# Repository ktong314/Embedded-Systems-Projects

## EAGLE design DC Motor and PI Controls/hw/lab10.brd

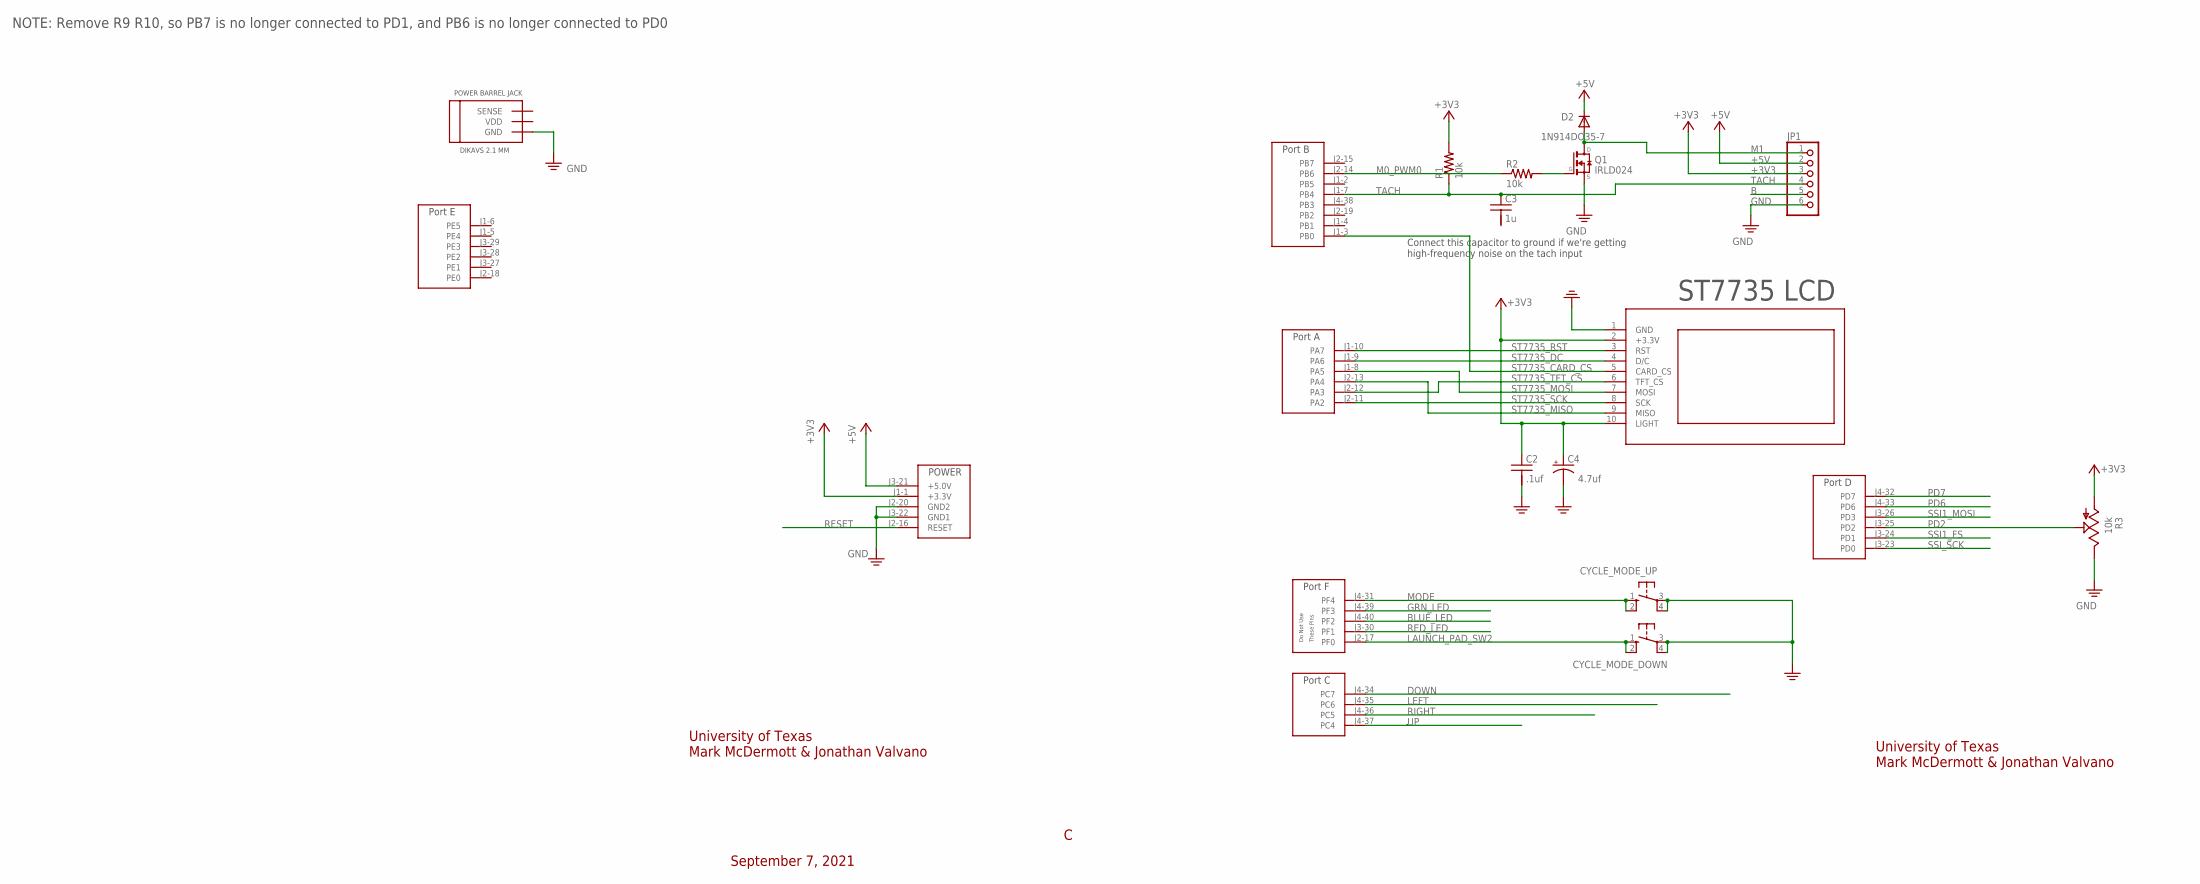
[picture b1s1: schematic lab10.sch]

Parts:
C2: .1uf; CAP200MIL
C3: 1u; CAP100MIL
C4: 4.7uf; CAP200MILPOLARIZED
CYCLE_MODE_DOWN: B3F-1052; B3F-10XX
CYCLE_MODE_UP: B3F-1052; B3F-10XX
D2: 1N914DO35-7; DO35-7
JP1: PINHD-1X6; 1X06
Q1: IRLD024
R1, R2: 10k; RES300MIL
R3: 10k; PTA2043
U$2: TM4C_BP; TM4C_BOOSTER_PACK
U$3: ST7735
U$4: 2.1MM_BARREL_JACK; 2.1M_BARREL_JACK

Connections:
+3V3: C2.1, C4.+, JP1.3, R1.2, R3.3 (A), U$2.J1-1 (+3.3V), U$3.2 (+3.3V), U$3.10 (LIGHT)
+5V: D2.C, JP1.2, U$2.J3-21 (+5.0V)
B: JP1.5
BLUE_LED: U$2.J4-40 (PF2)
DOWN: U$2.J4-34 (PC7)
GND: C2.2, C4.-, CYCLE_MODE_DOWN.3, CYCLE_MODE_DOWN.4 (P1), CYCLE_MODE_UP.3, CYCLE_MODE_UP.4 (P1), JP1.6, Q1.P$4 (S), R3.1 (E), U$2.J2-20 (GND2), U$2.J3-22 (GND1), U$3.1 (GND), U$4.GND
GRN_LED: U$2.J4-39 (PF3)
LAUNCH_PAD_SW2: CYCLE_MODE_DOWN.1 (S), CYCLE_MODE_DOWN.2 (S1), U$2.J2-17 (PF0)
LEFT: U$2.J4-35 (PC6)
M0_PWM0: R2.1, U$2.J2-14 (PB6)
M1: D2.A, JP1.1, Q1.P$1 (D)
MODE: CYCLE_MODE_UP.1 (S), CYCLE_MODE_UP.2 (S1), U$2.J4-31 (PF4)
unnamed: Q1.P$3 (G), R2.2
PD2: R3.2 (S), U$2.J3-25 (PD2)
PD6: U$2.J4-33 (PD6)
PD7: U$2.J4-32 (PD7)
RED_LED: U$2.J3-30 (PF1)
RESET: U$2.J2-16 (RESET)
RIGHT: U$2.J4-36 (PC5)
SSI1_FS: U$2.J3-24 (PD1)
SSI1_MOSI: U$2.J3-26 (PD3)
SSI_SCK: U$2.J3-23 (PD0)
ST7735_CARD_CS: U$2.J1-3 (PB0), U$3.5 (CARD_CS)
ST7735_DC: U$2.J1-9 (PA6), U$3.4 (D/C)
ST7735_MISO: U$2.J2-13 (PA4), U$3.9 (MISO)
ST7735_MOSI: U$2.J1-8 (PA5), U$3.7 (MOSI)
ST7735_RST: U$2.J1-10 (PA7), U$3.3 (RST)
ST7735_SCK: U$2.J2-11 (PA2), U$3.8 (SCK)
ST7735_TFT_CS: U$2.J2-12 (PA3), U$3.6 (TFT_CS)
TACH: C3.1, JP1.4, R1.1, U$2.J1-7 (PB4)
UP: U$2.J4-37 (PC4)

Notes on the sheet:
University of Texas Mark McDermott & Jonathan Valvano
September 7, 2021
ST7735 LCD
NOTE: Remove R9 R10, so PB7 is no longer connected to PD1, and PB6 is no longer connected to PD0
Connect this capacitor to ground if we're getting high-frequency noise on the tach input

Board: 2 copper layers, 14 parts (0 on the bottom side), 17 nets, no tracks yet.

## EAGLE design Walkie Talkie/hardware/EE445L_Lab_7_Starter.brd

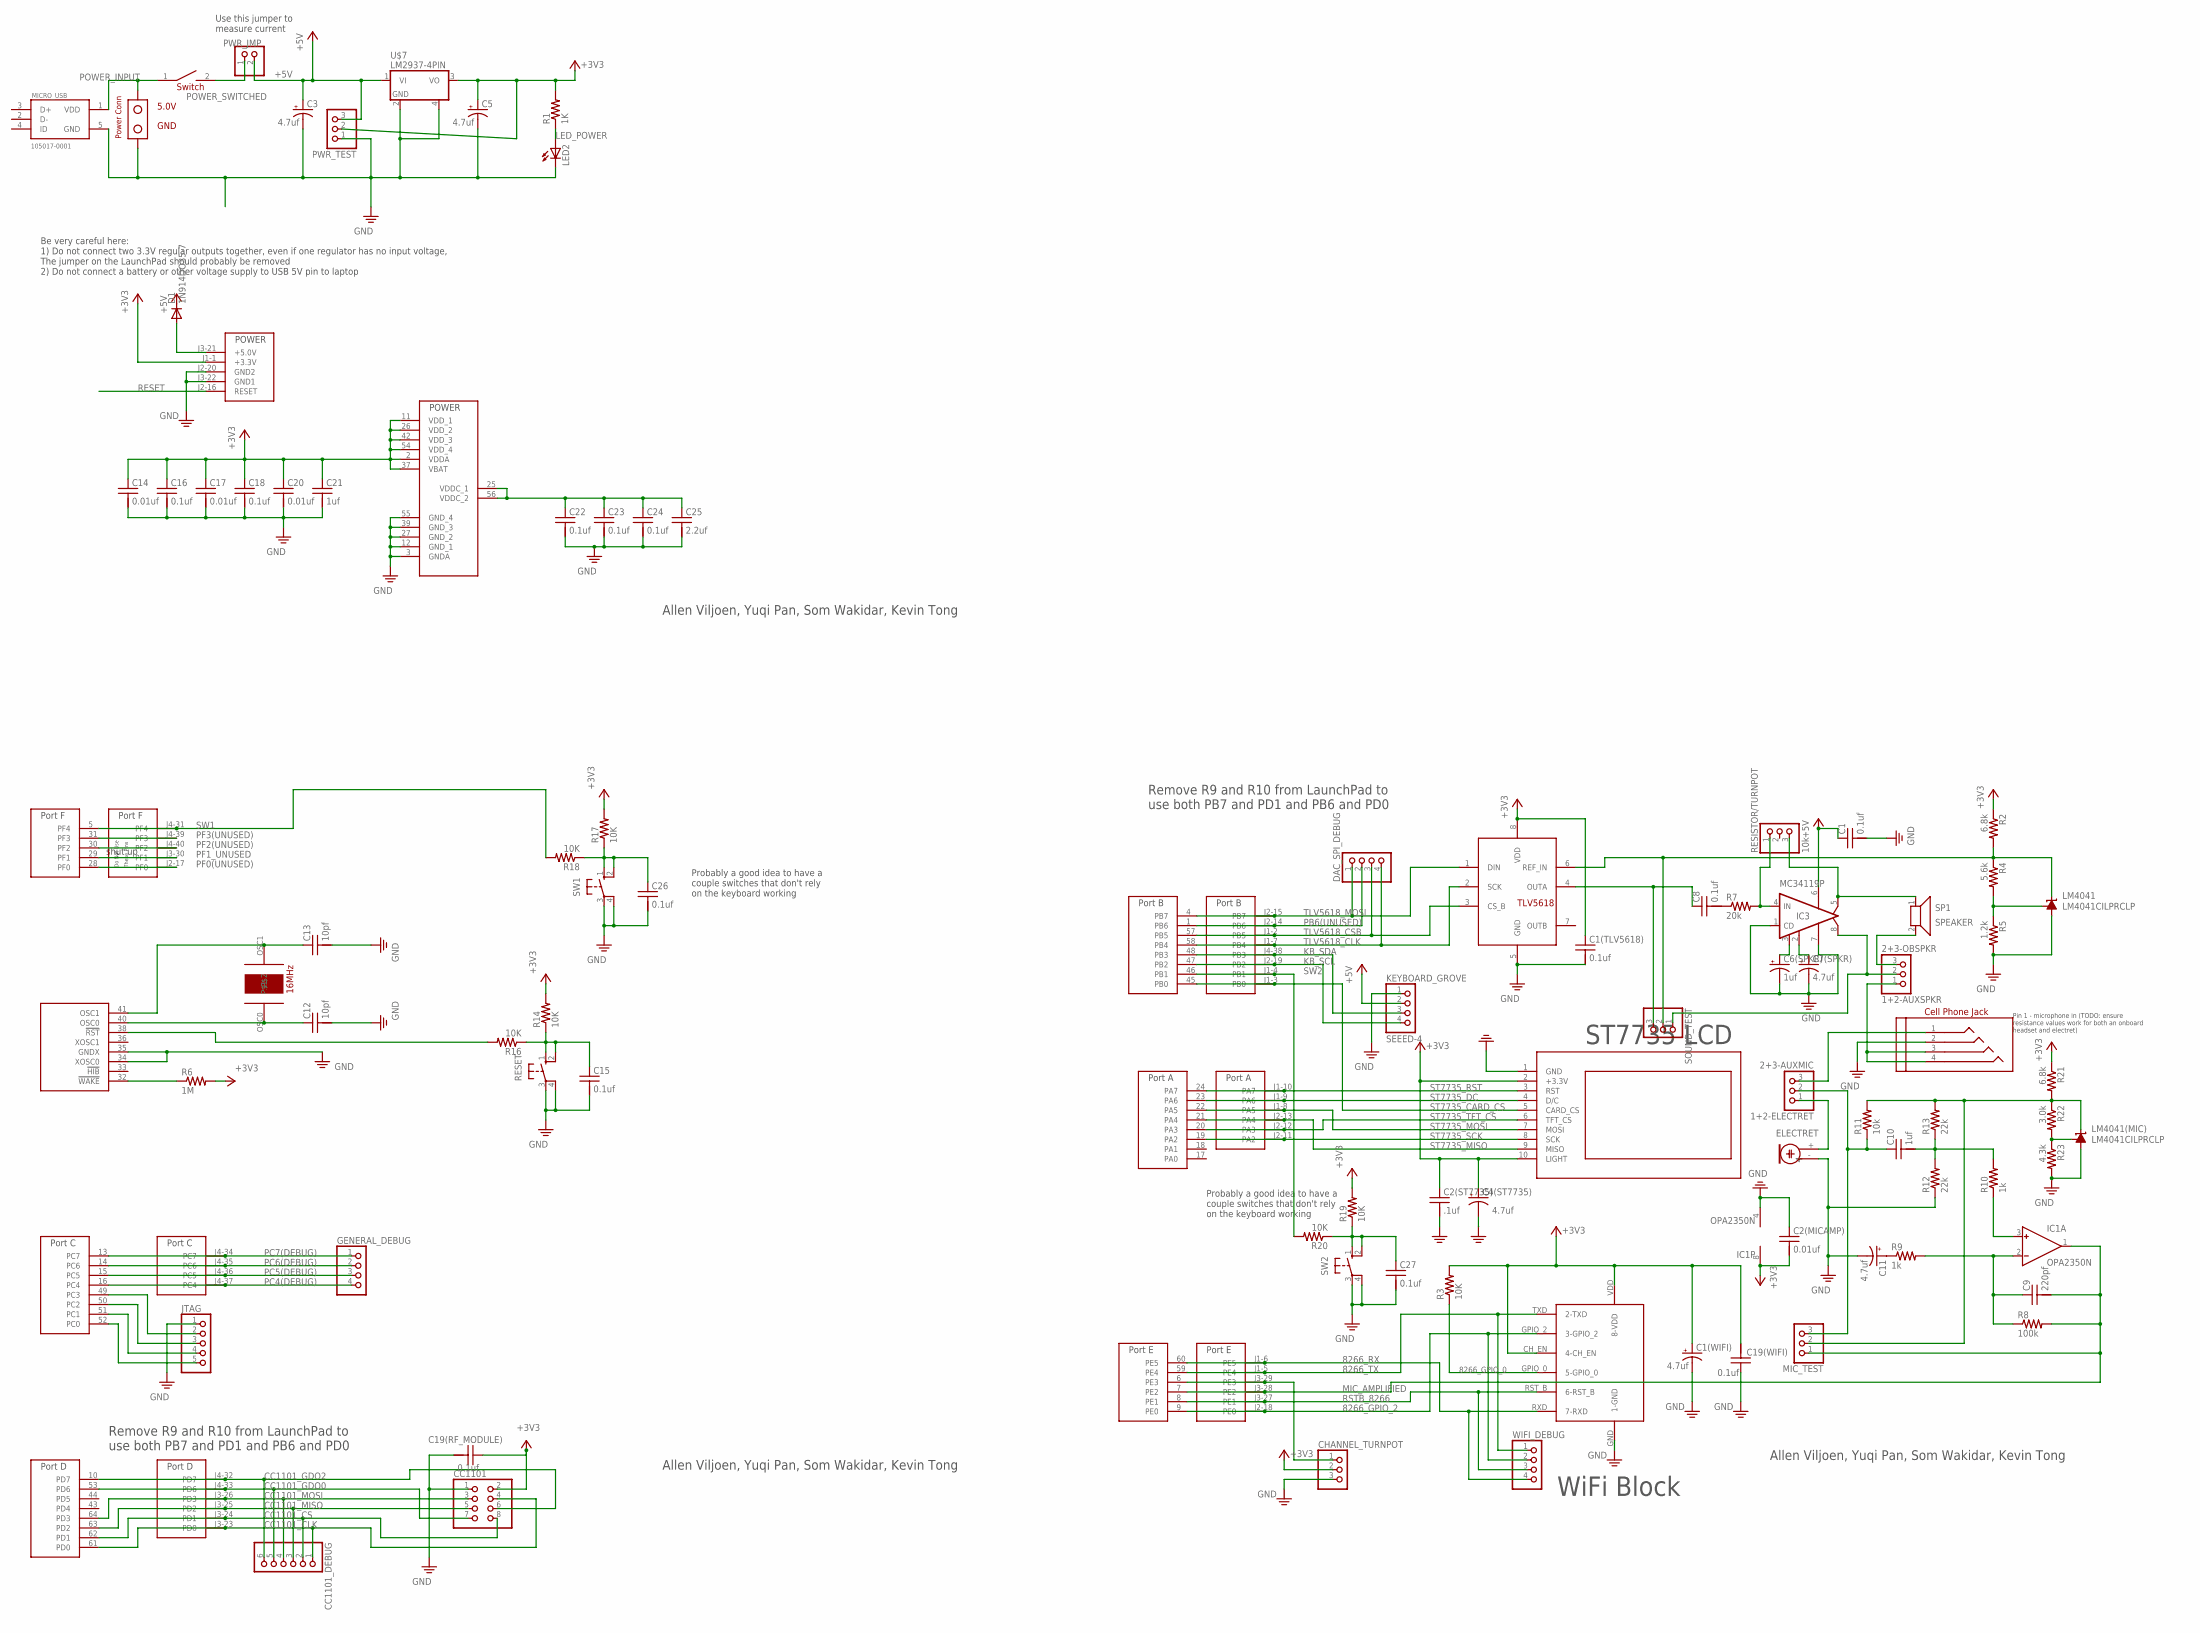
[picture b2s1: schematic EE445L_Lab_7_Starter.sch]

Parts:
1+2-AUXSPKR: 2+3-OBSPKR; 1X03
1+2-ELECTRET: 2+3-AUXMIC; 1X03
C1, C8, C15, C16, C18, C19(RF_MODULE), C22, C23, C24, C26, C27: 0.1uf; CAP100MIL
C1(TLV5618), C19(WIFI): 0.1uf; CAP200MIL
C1(WIFI), C3, C4(ST7735), C5, C7(SPKR), C11: 4.7uf; CAP200MILPOLARIZED
C2(MICAMP): 0.01uf; CAP200MIL
C2(ST7735): .1uf; CAP200MIL
C6(SPKR): 1uf; CAP200MILPOLARIZED
C9: 220pf; CAP200MIL
C10: 1uf; CAP200MIL
C12, C13: 10pf; CAP100MIL
C14, C17, C20: 0.01uf; CAP100MIL
C21: 1uf; CAP100MIL
C25: 2.2uf; CAP100MIL
CC1101: PINHD-2X4; 2X04
CC1101_DEBUG: PINHD-1X6; 1X06
CHANNEL_TURNPOT: PINHD-1X3; 1X03
D1: 1N914DO35-7; DO35-7
DAC_SPI_DEBUG: PINHD-1X4/90; 1X04/90
ELECTRET: ELECTRET; 9.7ELECTRET
GENERAL_DEBUG: PINHD-1X4/90; 1X04/90
IC1: OPA2350N; DIL08
IC3: MC34119P; DIL08
JTAG: PINHD-1X5; 1X05
KEYBOARD_GROVE: SEEED-4; 1_04X2MM
LED2: LED3MM
LM4041, LM4041(MIC): LM4041CILPRCLP; LP_O-PBCY-W3
MICRO_USB: 105017-0001; MOLEX_105017-0001
MIC_TEST: PINHD-1X3/90; 1X03/90
PWR_JMP: PINHD-1X2; 1X02
PWR_TEST: PINHD-1X3/90; 1X03/90
R1: 1K; RES200MIL
R2, R21: 6.8k; RES300MIL
R3: 10K; RES300MIL
R4: 5.6k; RES300MIL
R5: 1.2k; RES300MIL
R6: 1M; RES300MIL
R7: 20k; RES300MIL
R8: 100k; RES300MIL
R9, R10: 1k; RES300MIL
R11: 10k; RES300MIL
R12, R13: 22k; RES300MIL
R14, R16, R17, R18, R19, R20: 10K; RES200MIL
R22: 3.0k; RES300MIL
R23: 4.3k; RES300MIL
RESET: B3F-1052; B3F-10XX
RESISTOR/TURNPOT: 10k; 1X03/90
SOUND_TEST: PINHD-1X3/90; 1X03/90
SP1: SPEAKER; 1X02
ST7735: ST7735
SW1, SW2: B3F-1052; B3F-10XX
TLV5618: TLV5618; DIL08
U$1: ESP_8266; ESP8266
U$2: TM4C_BP; TM4C_BOOSTER_PACK
U$5: POWER_CONN
U$6: SW_POWER_100MIL; SW_POWER
U$7: LM2937-4PIN; TO220-4PIN
U$8: AUDIO_CONN_3.5MM
U$9: TM4C123GH6PM; QFP50P1200X1200X160-64N
WIFI_DEBUG: PINHD-1X4/90; 1X04/90
Y1: 16MHZ_CRYSTAL

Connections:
8266_GPIO_0: R3.1, U$1.GPIO_0 (5-GPIO_0)
8266_GPIO_2: U$1.GPIO_2 (3-GPIO_2), U$2.J2-18 (PE0), U$9.9 (PE0), WIFI_DEBUG.2
8266_RX: U$1.RXD (7-RXD), U$2.J1-6 (PE5), U$9.60 (PE5), WIFI_DEBUG.4
8266_TX: U$1.TXD (2-TXD), U$2.J1-5 (PE4), U$9.59 (PE4), WIFI_DEBUG.1
+3V3: C1(TLV5618).1, C1(WIFI).+, C2(MICAMP).2, C2(ST7735).1, C4(ST7735).+, C5.+, C14.1, C16.1, C17.1, C18.1, C19(RF_MODULE).1, C19(WIFI).2, C20.1, C21.1, CC1101.2, CHANNEL_TURNPOT.2, IC1.8 (V+), PWR_TEST.2, R1.2, R2.1, R3.2, R6.2, R14.2, R17.2, R19.2, R21.1, ST7735.2 (+3.3V), ST7735.10 (LIGHT), TLV5618.8 (VDD), U$1.CH_EN (4-CH_EN), U$1.VDD (8-VDD), U$2.J1-1 (+3.3V), U$7.3 (VO), U$9.2 (VDDA), U$9.11 (VDD_1), U$9.26 (VDD_2), U$9.37 (VBAT), U$9.42 (VDD_3), U$9.54 (VDD_4)
+5V: C1.1, C3.+, D1.C, IC3.6 (VCC), KEYBOARD_GROVE.2, PWR_JMP.2, PWR_TEST.3, U$7.1 (VI)
AUDIO_AMP_OUT: 1+2-AUXSPKR.2, IC3.8 (VO2), SOUND_TEST.1
AUX_AUDIO: 1+2-AUXSPKR.1, U$8.3, U$8.4
AUX_MIC: 1+2-ELECTRET.3, U$8.1
CC1101_CLK: CC1101.4, CC1101_DEBUG.1, U$2.J3-23 (PD0), U$9.61 (PD0)
CC1101_CS: CC1101.8, CC1101_DEBUG.2, U$2.J3-24 (PD1), U$9.62 (PD1)
CC1101_GDO0: CC1101.7, CC1101_DEBUG.5, U$2.J4-33 (PD6), U$9.53 (PD6)
CC1101_GDO2: CC1101.6, CC1101_DEBUG.6, U$2.J4-32 (PD7), U$9.10 (PD7)
CC1101_MISO: CC1101.5, CC1101_DEBUG.3, U$2.J3-25 (PD2), U$9.63 (PD2)
CC1101_MOSI: CC1101.3, CC1101_DEBUG.4, U$2.J3-26 (PD3), U$9.64 (PD3)
CHANNEL_TURNPOT: CHANNEL_TURNPOT.1, U$2.J3-29 (PE3), U$9.6 (PE3)
DAC_OUT: C8.1, SOUND_TEST.3, TLV5618.4 (OUTA)
ELECTRET_MIC: 1+2-ELECTRET.1, ELECTRET.+ (2)
GND: C1.2, C1(TLV5618).2, C1(WIFI).-, C2(MICAMP).1, C2(ST7735).2, C3.-, C4(ST7735).-, C5.-, C6(SPKR).-, C7(SPKR).-, C11.-, C12.2, C13.2, C14.2, C15.2, C16.2, C17.2, C18.2, C19(RF_MODULE).2, C19(WIFI).1, C20.2, C21.2, C22.2, C23.2, C24.2, C25.2, C26.2, C27.2, CC1101.1, CHANNEL_TURNPOT.3, ELECTRET.- (1), IC1.4 (V-), IC3.1 (CD), IC3.7 (GND), JTAG.1, KEYBOARD_GROVE.1, LED2.K (C), LM4041.3 (A), LM4041(MIC).3 (A), MICRO_USB.5 (GND), PWR_TEST.1, R5.2, R12.1, R23.2, RESET.3, RESET.4 (P1), ST7735.1 (GND), SW1.3, SW1.4 (P1), SW2.3, SW2.4 (P1), TLV5618.5 (GND), U$1.GND (1-GND), U$2.J2-20 (GND2), U$2.J3-22 (GND1), U$5.GND, U$7.2 (GND), U$7.4 (PAD), U$8.2, U$9.3 (GNDA), U$9.12 (GND_1), U$9.27 (GND_2), U$9.34 (XOSC0), U$9.35 (GNDX), U$9.39 (GND_3), U$9.55 (GND_4)
ICDI-TCK/SWCLK: JTAG.5, U$9.52 (PC0)
ICDI-TDI: JTAG.3, U$9.50 (PC2)
ICDI-TDO/SWO: JTAG.2, U$9.49 (PC3)
ICDI-TMS/SWDIO: JTAG.4, U$9.51 (PC1)
KB_SCL: KEYBOARD_GROVE.4, U$2.J2-19 (PB2), U$9.47 (PB2)
KB_SDA: KEYBOARD_GROVE.3, U$2.J4-38 (PB3), U$9.48 (PB3)
LED_POWER: LED2.A, R1.1
MIC_AMPLIFIED: C9.2, IC1.1 (OUT), MIC_TEST.1, R8.2, U$2.J3-28 (PE2), U$9.7 (PE2)
MIC_FEEDBACK/GND: C9.1, IC1.2 (IN-), R8.1, R9.2
MIC_FILTER: C10.2, R10.2, R12.2, R13.1
MIC_FILTERED: IC1.3 (IN+), R10.1
MIC_OUT_RAW: 1+2-ELECTRET.2, C10.1, MIC_TEST.3, R11.1
MIC_REF: LM4041(MIC).2 (C), MIC_TEST.2, R11.2, R13.2, R21.2, R22.1
MIC_REF_FB: LM4041(MIC).1 (FB), R22.2, R23.1
unnamed: C8.2, R7.1
unnamed: C11.+, R9.1
unnamed: D1.A, U$2.J3-21 (+5.0V)
OSC0: C12.1, U$9.40 (OSC0), Y1.OSC0
OSC1: C13.1, U$9.41 (OSC1), Y1.OSC1
PB6(UNUSED): DAC_SPI_DEBUG.2, U$2.J2-14 (PB6), U$9.1 (PB6)
PC4(DEBUG): GENERAL_DEBUG.4, U$2.J4-37 (PC4), U$9.16 (PC4)
PC5(DEBUG): GENERAL_DEBUG.3, U$2.J4-36 (PC5), U$9.15 (PC5)
PC6(DEBUG): GENERAL_DEBUG.2, U$2.J4-35 (PC6), U$9.14 (PC6)
PC7(DEBUG): GENERAL_DEBUG.1, U$2.J4-34 (PC7), U$9.13 (PC7)
PF0(UNUSED): U$2.J2-17 (PF0), U$9.28 (PF0)
PF1_UNUSED: U$2.J3-30 (PF1), U$9.29 (PF1)
PF2(UNUSED): U$2.J4-40 (PF2), U$9.30 (PF2)
PF3(UNUSED): U$2.J4-39 (PF3), U$9.31 (PF3)
POWER_INPUT: MICRO_USB.1 (VDD), U$5.VDD, U$6.1
POWER_SWITCHED: PWR_JMP.1, U$6.2
RESET: U$2.J2-16 (RESET)
RESET_DEBOUNCE: C15.1, R14.1, R16.1, RESET.1 (S), RESET.2 (S1)
RESET_IN: R16.2, U$9.38 (!RST)
RSTB_8266: U$1.RST_B (6-RST_B), U$2.J3-27 (PE1), U$9.8 (PE1), WIFI_DEBUG.3
SPKRAMP_GND0: C7(SPKR).+, IC3.2 (FC2)
SPKRAMP_GND1: C6(SPKR).+, IC3.3 (FC1)
SPKRAMP_OUT: IC3.5 (VO1), RESISTOR/TURNPOT.3, SP1.1
SPKRAMP_TURNPOT: IC3.4 (IN), R7.2, RESISTOR/TURNPOT.1
SPKR_OUT: 1+2-AUXSPKR.3, SP1.2
ST7735_CARD_CS: ST7735.5 (CARD_CS), U$2.J1-3 (PB0), U$9.45 (PB0)
ST7735_DC: ST7735.4 (D/C), U$2.J1-9 (PA6), U$9.23 (PA6)
ST7735_MISO: ST7735.9 (MISO), U$2.J2-13 (PA4), U$9.21 (PA4)
ST7735_MOSI: ST7735.7 (MOSI), U$2.J1-8 (PA5), U$9.22 (PA5)
ST7735_RST: ST7735.3 (RST), U$2.J1-10 (PA7), U$9.24 (PA7)
ST7735_SCK: ST7735.8 (SCK), U$2.J2-11 (PA2), U$9.19 (PA2)
ST7735_TFT_CS: ST7735.6 (TFT_CS), U$2.J2-12 (PA3), U$9.20 (PA3)
SW1: R18.2, U$2.J4-31 (PF4), U$9.5 (PF4)
SW1_DEBOUNCE: C26.1, R17.1, R18.1, SW1.1 (S), SW1.2 (S1)
SW2: R20.2, U$2.J1-4 (PB1), U$9.46 (PB1)
SW2_DEBOUNCE: C27.1, R19.1, R20.1, SW2.1 (S), SW2.2 (S1)
TLV5616_REF_FB: LM4041.1 (FB), R4.2, R5.1
TLV5618_CLK: DAC_SPI_DEBUG.4, TLV5618.2 (SCK), U$2.J1-7 (PB4), U$9.58 (PB4)
TLV5618_CSB: DAC_SPI_DEBUG.3, TLV5618.3 (CS_B), U$2.J1-2 (PB5), U$9.57 (PB5)
TLV5618_MOSI: DAC_SPI_DEBUG.1, TLV5618.1 (DIN), U$2.J2-15 (PB7), U$9.4 (PB7)
TLV5618_REF: LM4041.2 (C), R2.2, R4.1, SOUND_TEST.2, TLV5618.6 (REF_IN)
VDDC: C22.1, C23.1, C24.1, C25.1, U$9.25 (VDDC_1), U$9.56 (VDDC_2)
WAKE: R6.1, U$9.32 (!WAKE)

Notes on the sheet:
WiFi Block
ST7735 LCD
Use this jumper to measure current
Remove R9 and R10 from LaunchPad to use both PB7 and PD1 and PB6 and PD0
Allen Viljoen, Yuqi Pan, Som Wakidar, Kevin Tong
Be very careful here: 1) Do not connect two 3.3V regular outputs together, even if one regulator has no input voltage, The jumper on the LaunchPad should probably be removed 2) Do not connect a battery or other voltage supply to USB 5V pin to laptop
Pin 1 - microphone in (TODO: ensure resistance values work for both an onboard headset and electret)
shut up
Probably a good idea to have a couple switches that don't rely on the keyboard working

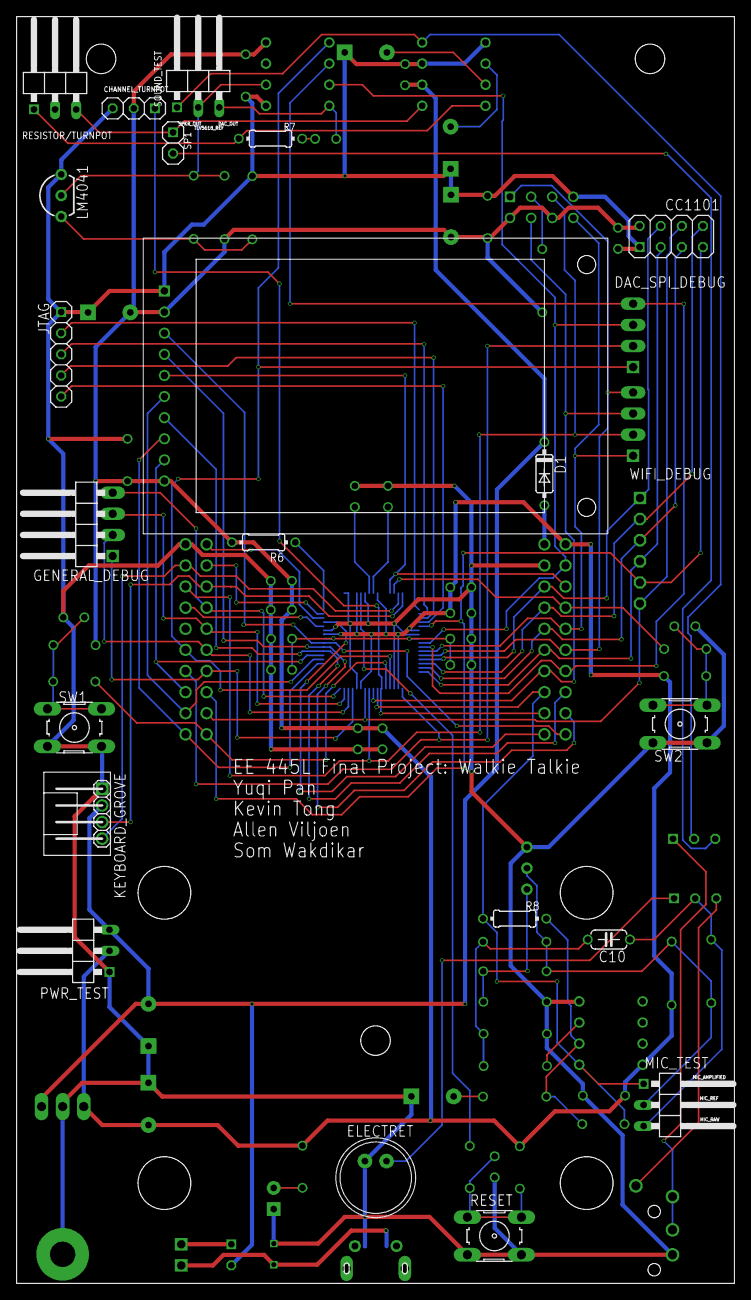
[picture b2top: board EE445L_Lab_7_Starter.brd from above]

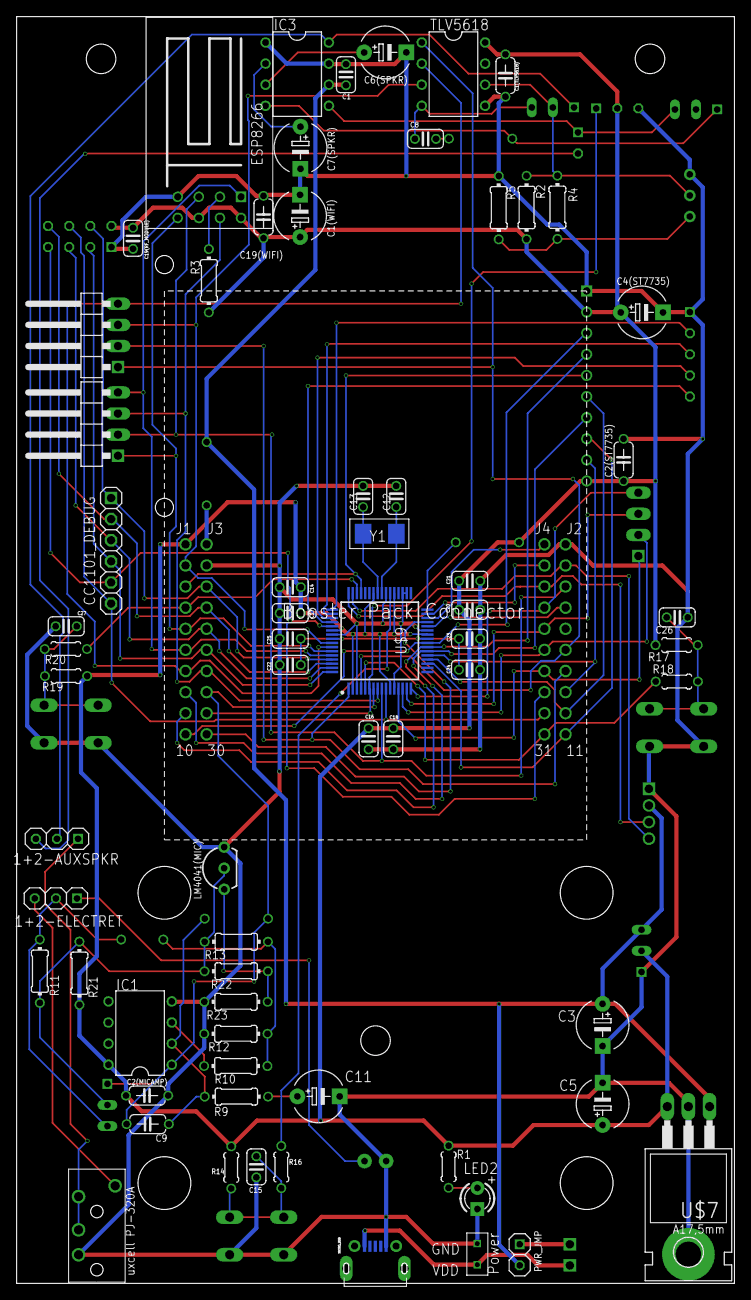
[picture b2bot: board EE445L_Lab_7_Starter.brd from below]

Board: 2 copper layers, 86.4 x 152.4 mm, 90 parts (68 on the bottom side), 75 nets.

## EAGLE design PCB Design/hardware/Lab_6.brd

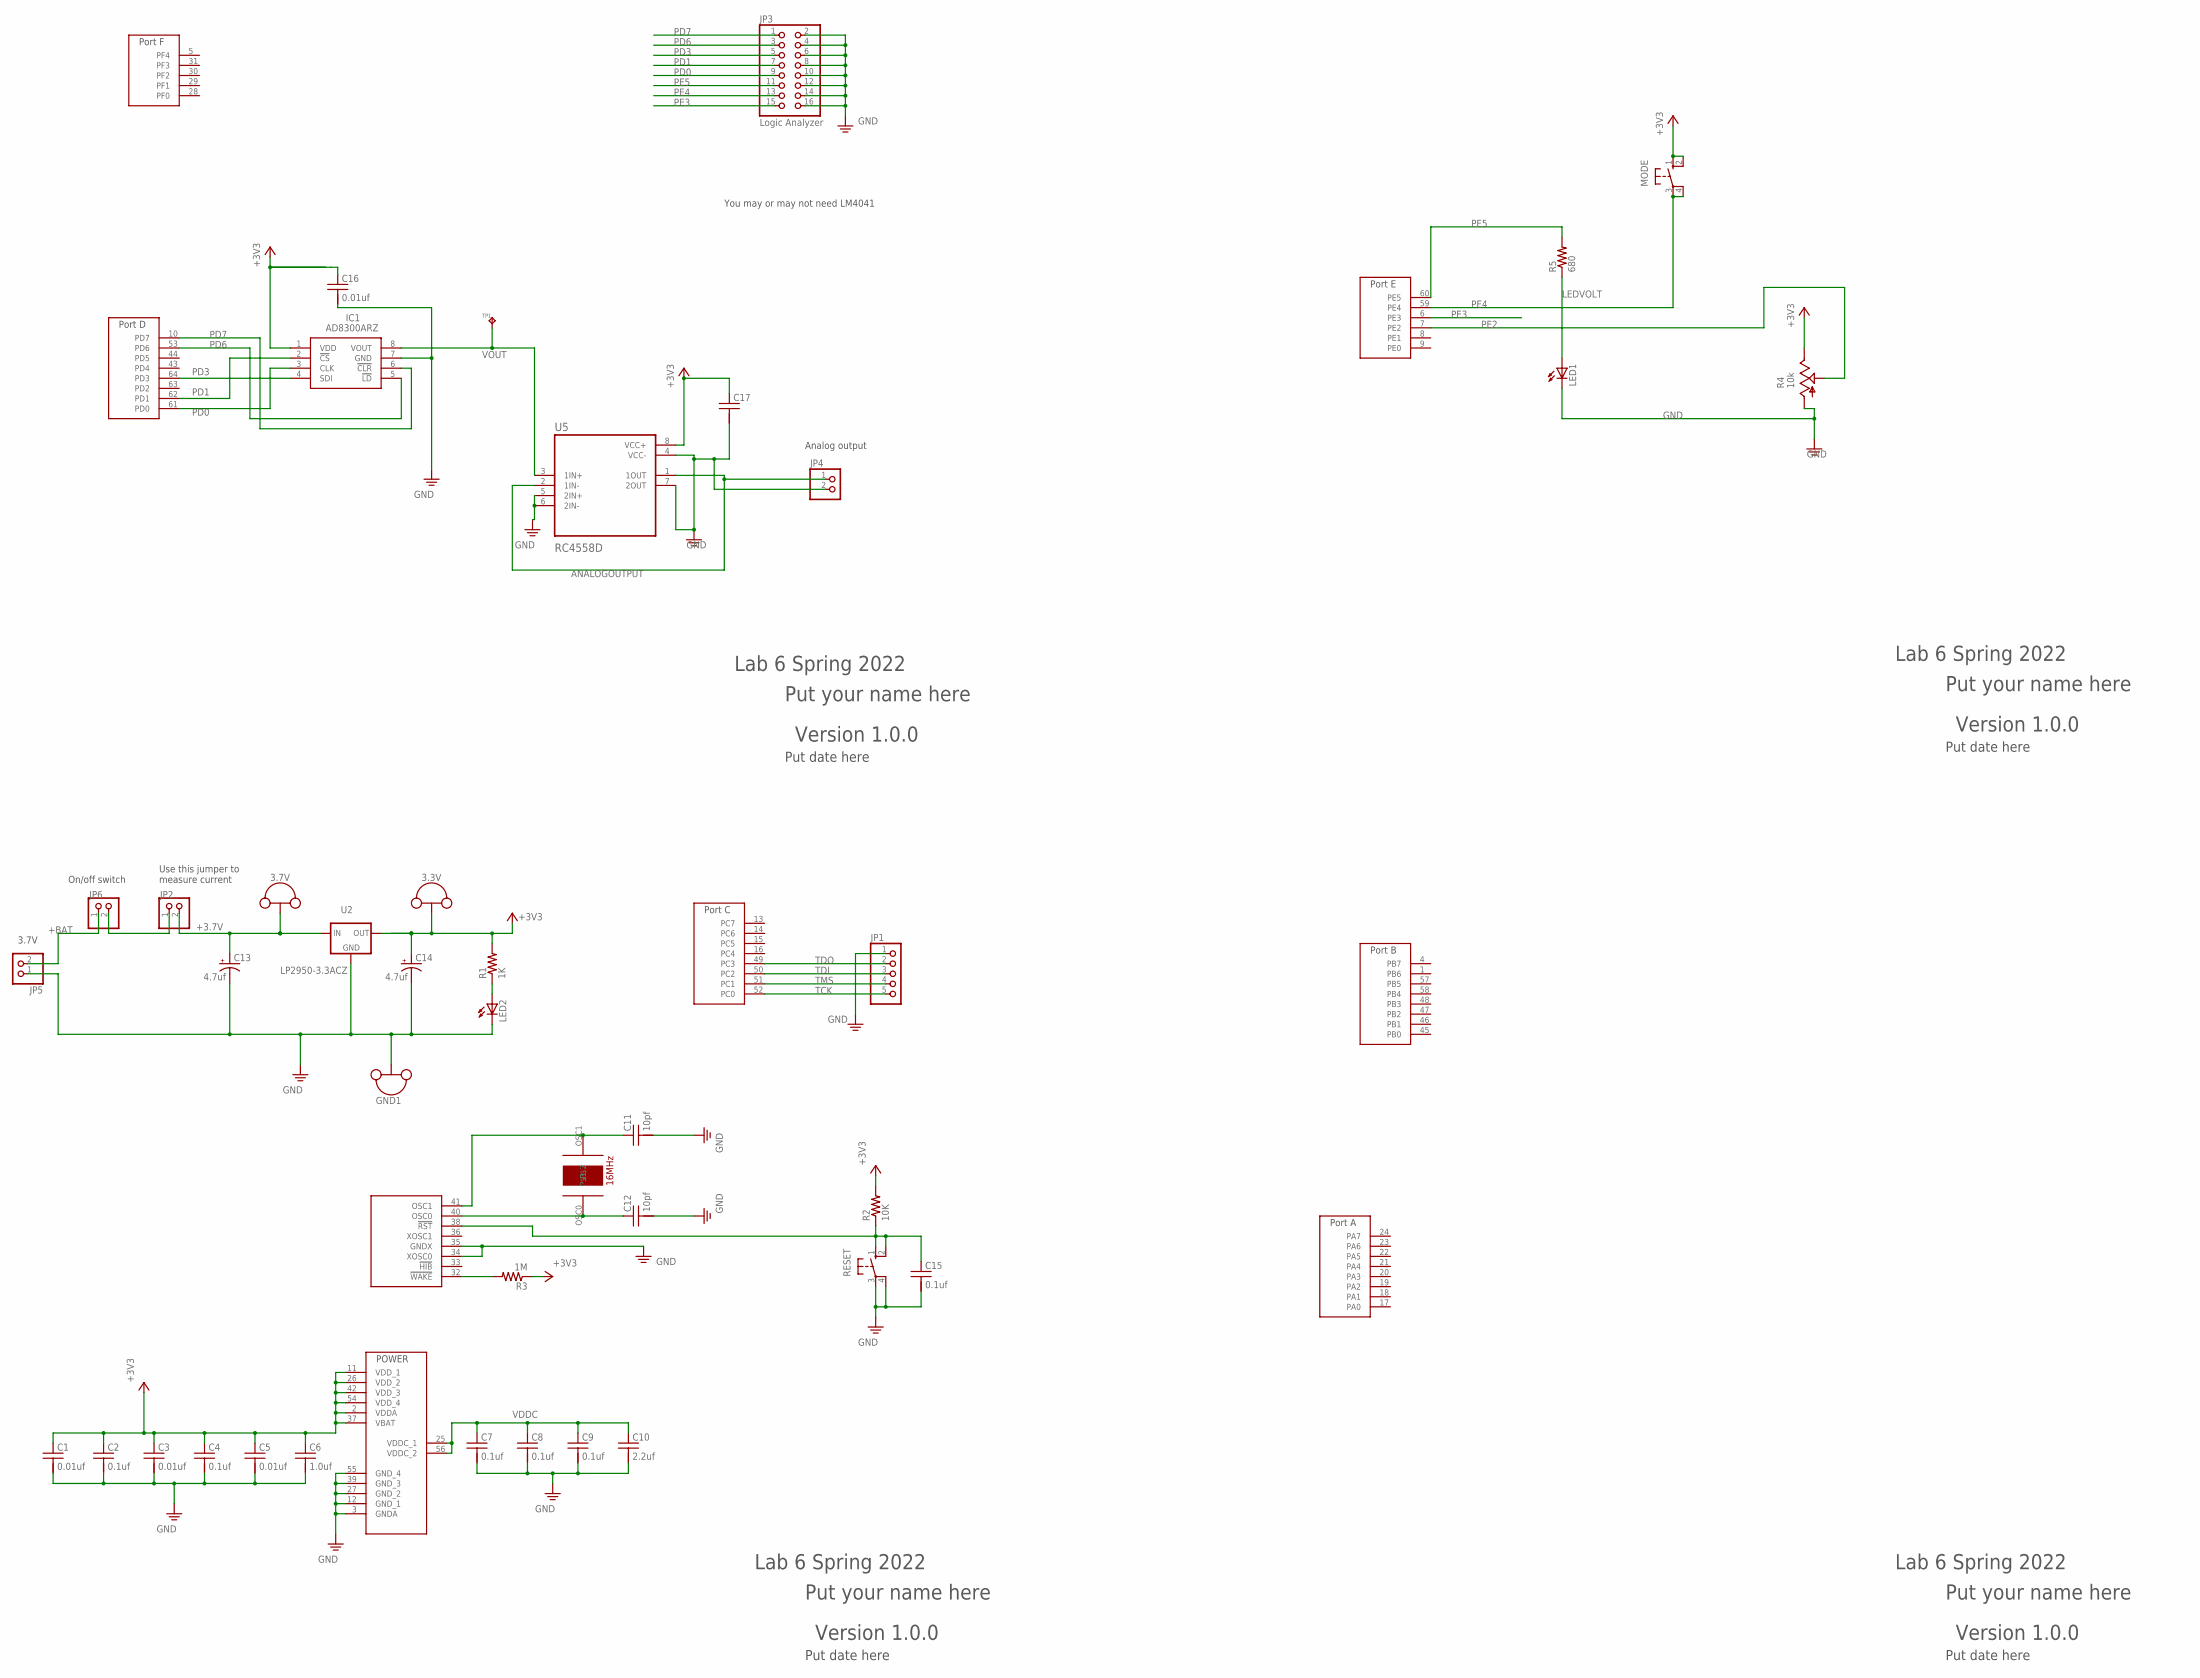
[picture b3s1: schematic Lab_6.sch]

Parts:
3.3V, 3.7V: TP_LOOP
C1, C3, C5, C16, C17: 0.01uf; CAP100MIL
C2, C4, C7, C8, C9, C15: 0.1uf; CAP100MIL
C6: 1.0uf; CAP100MIL
C10: 2.2uf; CAP100MIL
C11, C12: 10pf; CAP100MIL
C13, C14: 4.7uf; CAP200MILPOLARIZED
GND1: TP_LOOP
IC1: AD8300ARZ; SOIC127P600X175-8N
JP1: PINHD-1X5; 1X05
JP2, JP4, JP5, JP6: PINHD-1X2; 1X02
JP3: Logic Analyzer; 2X08
LED1, LED2: LED3MM
MODE: B3F-1052; B3F-10XX
R1: 1K; RES200MIL
R2: 10K; RES200MIL
R3: 1M; RES200MIL
R4: 10k; PTA2043
R5: 680; RES200MIL
RESET: B3F-1052; B3F-10XX
TP1: TP_KEYSTONE500X; P1.1MM
U1: TM4C123GH6PM; QFP50P1200X1200X160-64N
U2: LP2950-3.3ACZ; TO92
U5: RC4558D; SOIC127P599X175-8N
Y1: 16MHZ_CRYSTAL

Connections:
+3.7V: 3.7V.P$1, 3.7V.P$2, C13.+, JP2.2, U2.3 (IN)
+3V3: 3.3V.P$1, 3.3V.P$2, C1.1, C2.1, C3.1, C4.1, C5.1, C6.1, C14.+, C16.1, C17.1, IC1.1 (VDD), MODE.1 (S), MODE.2 (S1), R1.2, R2.2, R3.1, R4.1 (E), U1.2 (VDDA), U1.11 (VDD_1), U1.26 (VDD_2), U1.37 (VBAT), U1.42 (VDD_3), U1.54 (VDD_4), U2.1 (OUT), U5.8 (VCC+)
+BAT: JP5.2, JP6.1
ANALOGOUTPUT: JP4.1, U5.1 (1OUT), U5.2 (1IN-)
GND: C1.2, C2.2, C3.2, C4.2, C5.2, C6.2, C7.2, C8.2, C9.2, C10.2, C11.2, C12.2, C13.-, C14.-, C15.2, C16.2, C17.2, GND1.P$1, GND1.P$2, IC1.7 (GND), JP1.1, JP3.2, JP3.4, JP3.6, JP3.8, JP3.10, JP3.12, JP3.14, JP3.16, JP4.2, JP5.1, LED1.K (C), LED2.K (C), R4.3 (A), RESET.3, RESET.4 (P1), U1.3 (GNDA), U1.12 (GND_1), U1.27 (GND_2), U1.34 (XOSC0), U1.35 (GNDX), U1.39 (GND_3), U1.55 (GND_4), U2.2 (GND), U5.4 (VCC-), U5.5 (2IN+), U5.6 (2IN-), U5.7 (2OUT)
LEDVOLT: LED1.A, R5.1
OSC0: C12.1, U1.40 (OSC0), Y1.OSC0
OSC1: C11.1, U1.41 (OSC1), Y1.OSC1
PD0: IC1.3 (CLK), JP3.9, U1.61 (PD0)
PD1: IC1.2 (!CS), JP3.7, U1.62 (PD1)
PD3: IC1.4 (SDI), JP3.5, U1.64 (PD3)
PD6: IC1.5 (!LD), JP3.3, U1.53 (PD6)
PD7: IC1.6 (!CLR), JP3.1, U1.10 (PD7)
PE2: R4.2 (S), U1.7 (PE2)
PE3: JP3.15, U1.6 (PE3)
PE4: JP3.13, MODE.3, MODE.4 (P1), U1.59 (PE4)
PE5: JP3.11, R5.2, U1.60 (PE5)
POWERLED: LED2.A, R1.1
RESET: C15.1, R2.1, RESET.1 (S), RESET.2 (S1), U1.38 (!RST)
SWITCHEDPOWER: JP2.1, JP6.2
TCK: JP1.5, U1.52 (PC0)
TDI: JP1.3, U1.50 (PC2)
TDO: JP1.2, U1.49 (PC3)
TMS: JP1.4, U1.51 (PC1)
VDDC: C7.1, C8.1, C9.1, C10.1, U1.25 (VDDC_1), U1.56 (VDDC_2)
VOUT: IC1.8 (VOUT), TP1.TP, U5.3 (1IN+)
WAKE: R3.2, U1.32 (!WAKE)

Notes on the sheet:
Use this jumper to measure current
Lab 6 Spring 2022
Put your name here
Version 1.0.0
Put date here
You may or may not need LM4041
3.7V
Analog output
On/off switch

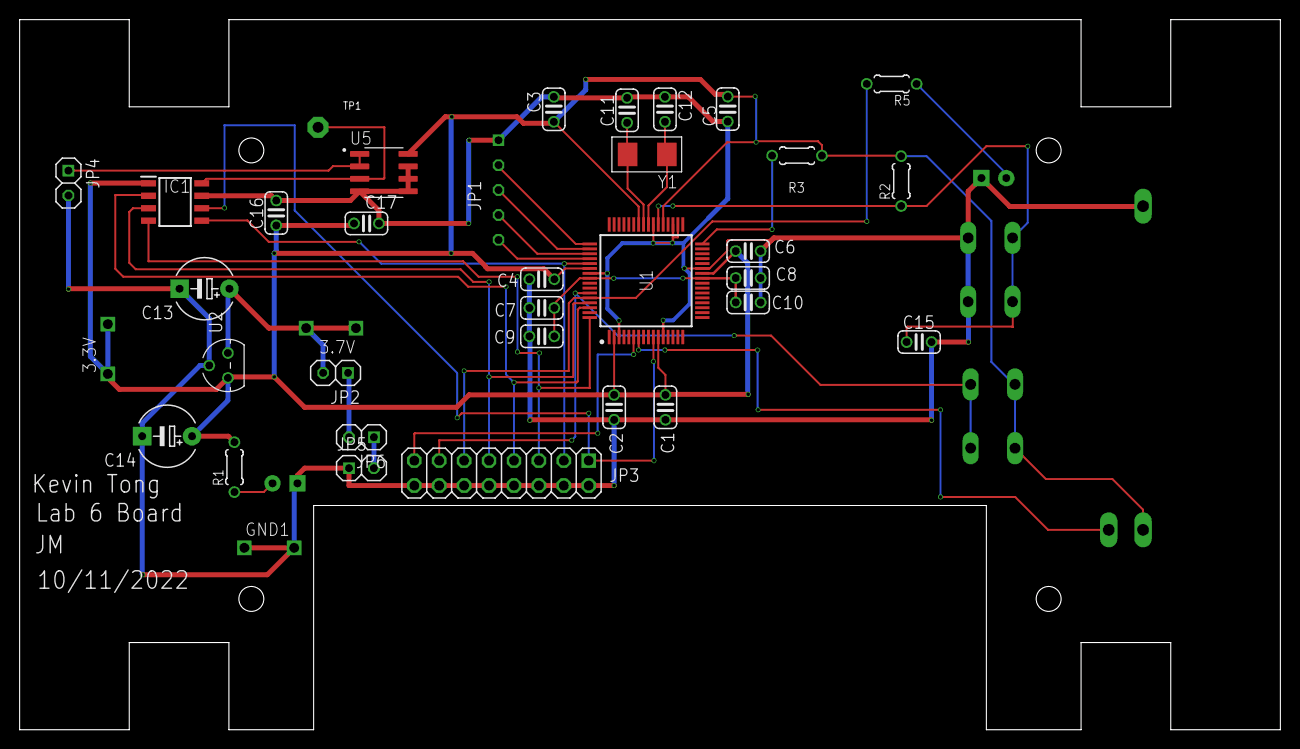
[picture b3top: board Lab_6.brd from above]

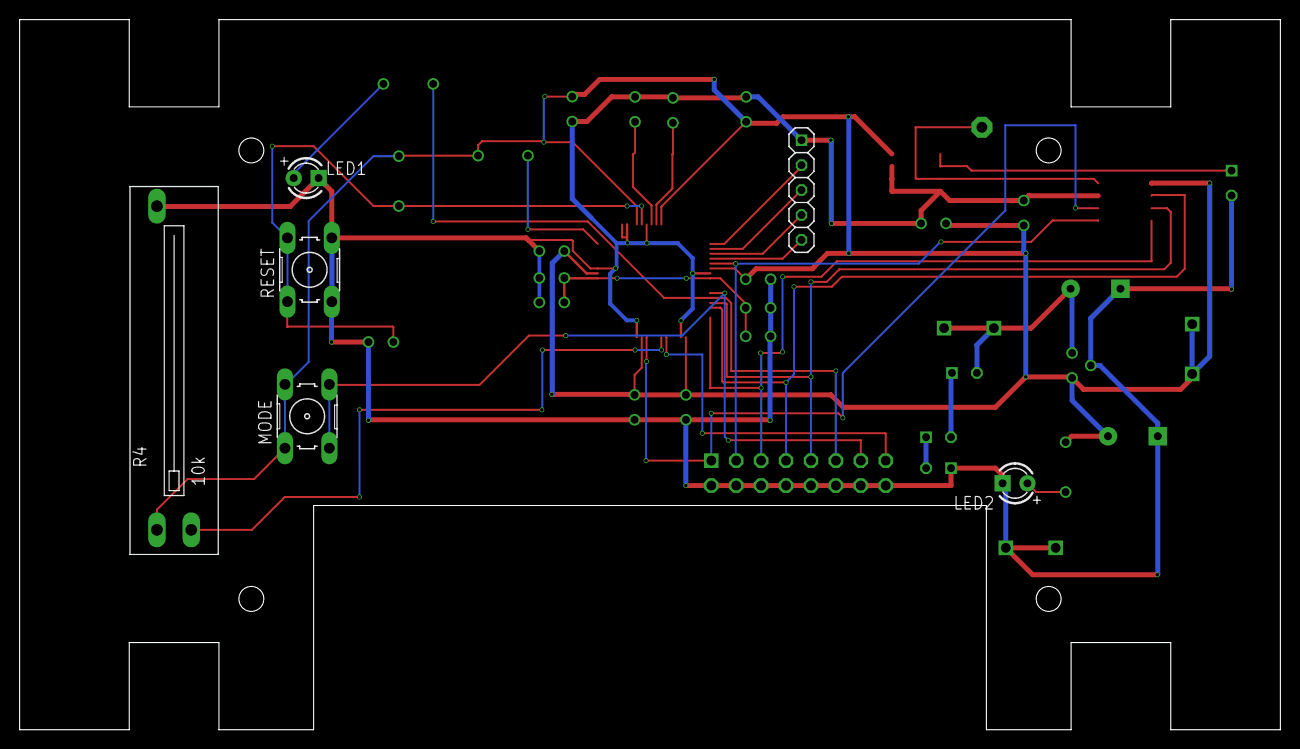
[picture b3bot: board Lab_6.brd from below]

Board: 2 copper layers, 128.5 x 72.4 mm, 41 parts (6 on the bottom side), 27 nets.

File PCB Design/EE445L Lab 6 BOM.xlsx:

Part | Value | Device | Package | Description | Price | Estimated Current
3.3V | TP_LOOP | TP_LOOP | TP_LOOP
3.7V | TP_LOOP | TP_LOOP | TP_LOOP |  | 8.0
C1 | 0.01uf | CAPACITOR025-024X044 | CAP100MIL | CAPACITOR, American symbol | 0.4
C2 | 0.1uf | CAPACITOR025-024X044 | CAP100MIL | CAPACITOR, American symbol | 0.05
C3 | 0.01uf | CAPACITOR025-024X044 | CAP100MIL | CAPACITOR, American symbol | 0.4
C4 | 0.1uf | CAPACITOR025-024X044 | CAP100MIL | CAPACITOR, American symbol | 0.05
C5 | 0.01uf | CAPACITOR025-024X044 | CAP100MIL | CAPACITOR, American symbol | 0.4
C6 | 1.0uf | CAPACITOR025-024X044 | CAP100MIL | CAPACITOR, American symbol | 0.47
C7 | 0.1uf | CAPACITOR025-024X044 | CAP100MIL | CAPACITOR, American symbol | 0.05
C8 | 0.1uf | CAPACITOR025-024X044 | CAP100MIL | CAPACITOR, American symbol | 0.05
C9 | 0.1uf | CAPACITOR025-024X044 | CAP100MIL | CAPACITOR, American symbol | 0.05
C10 | 2.2uf | CAPACITOR025-024X044 | CAP100MIL | CAPACITOR, American symbol | 0.4
C11 | 10pf | CAPACITOR025-024X044 | CAP100MIL | CAPACITOR, American symbol | 0.31
C12 | 10pf | CAPACITOR025-024X044 | CAP100MIL | CAPACITOR, American symbol | 0.31
C13 | 4.7uf | CAPACITOR_POLARIZEDE5-6 | CAP200MILPOLARIZED | POLARIZED CAPACITOR, American symbol | 0.4
C14 | 4.7uf | CAPACITOR_POLARIZEDE5-6 | CAP200MILPOLARIZED | POLARIZED CAPACITOR, American symbol | 0.4
C15 | 0.1uf | CAPACITOR025-024X044 | CAP100MIL | CAPACITOR, American symbol | 0.05
C16 | 0.01uf | CAPACITOR025-024X044 | CAP100MIL | CAPACITOR, American symbol | 0.4
C17 | 0.01uf | CAPACITOR025-024X044 | CAP100MIL | CAPACITOR, American symbol | 0.4
GND1 | TP_LOOP | TP_LOOP | TP_LOOP
IC1 | AD8300ARZ | AD8300ARZ | SOIC127P600X175-8N | DAC 1-Ch R-2R 12-Bit 8-Pin SOIC | 20.4 | 115 uA
JP1 |  | PINHD-1X5 | 1X05 | PIN HEADER
JP2 |  | PINHD-1X2 | 1X02 | PIN HEADER
JP3 | Logic Analyzer | PINHD-2X8 | 2X08 | PIN HEADER | 0.27
JP4 |  | PINHD-1X2 | 1X02 | PIN HEADER
JP5 |  | PINHD-1X2 | 1X02 | PIN HEADER
JP6 |  | PINHD-1X2 | 1X02 | PIN HEADER
LED1 |  | LED3MM | LED3MM | Avago Technologies LED | 0.29 | 4.85 mA
LED2 |  | LED3MM | LED3MM | Avago Technologies LED | 0.29 | 3.3 mA
MODE |  | B3F-1052 | B3F-10XX | OMRON SWITCH | 0.38
R1 | 1K | RESISTOR0204/5 | RES200MIL | RESISTOR, American symbol | 0.02
R2 | 10K | RESISTOR0204/5 | RES200MIL | RESISTOR, American symbol | 0.02
R3 | 1M | RESISTOR0204/5 | RES200MIL | RESISTOR, American symbol | 0.02
R4 | 10k | POTENTIOMETER_PTA2043B25U | PTA2043 | POTENTIOMETER | 1.28
R5 | 680.0 | RESISTOR0204/5 | RES200MIL | RESISTOR, American symbol | 0.02
RESET |  | B3F-1052 | B3F-10XX | OMRON SWITCH | 0.38
U1 | TM4C123GH6PM | TM4C123GH6PM | QFP50P1200X1200X160-64N |  | 11.31 | 2 mA
U2 | LP2950-3.3ACZ | LP2950-3.3ACZ | TO92 | LP2950 3.3V regulator, 100 mA TO-92 | 0.19
U5 | RC4558D | RC4558D | SOIC127P599X175-8N | Dual, 30-V, 3-MHz, low noise (8-nV/√Hz) operational amplifier | 0.76 | 3 mA
Y1 | 16MHZ_CRYSTAL | 16MHZ_CRYSTAL | 16MHZ_CRYSTAL
 |  |  |  |  | 48.22 | 13.265 mA

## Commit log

2022-09-13 added project 1
2022-09-13 added project 2
2022-09-13 removed useless files
2022-09-13 rename
2022-09-16 added lab2 report
2022-09-20 added alarm clock lab
2022-09-20 added videogame project
2022-09-30 added lab4
2022-09-30 removed lab4
2022-10-10 added project 5
2022-10-13 added lab6
2022-10-13 fixed lab6
2022-11-09 added lab9
2022-12-07 added lab10 and final project
